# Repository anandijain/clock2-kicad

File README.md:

# clock2-kicad

the ben eater clock module as a pcb

I'm not sure why the placement of the resistors, caps, and 555s (and a few other things) is wrong in the 3D file.

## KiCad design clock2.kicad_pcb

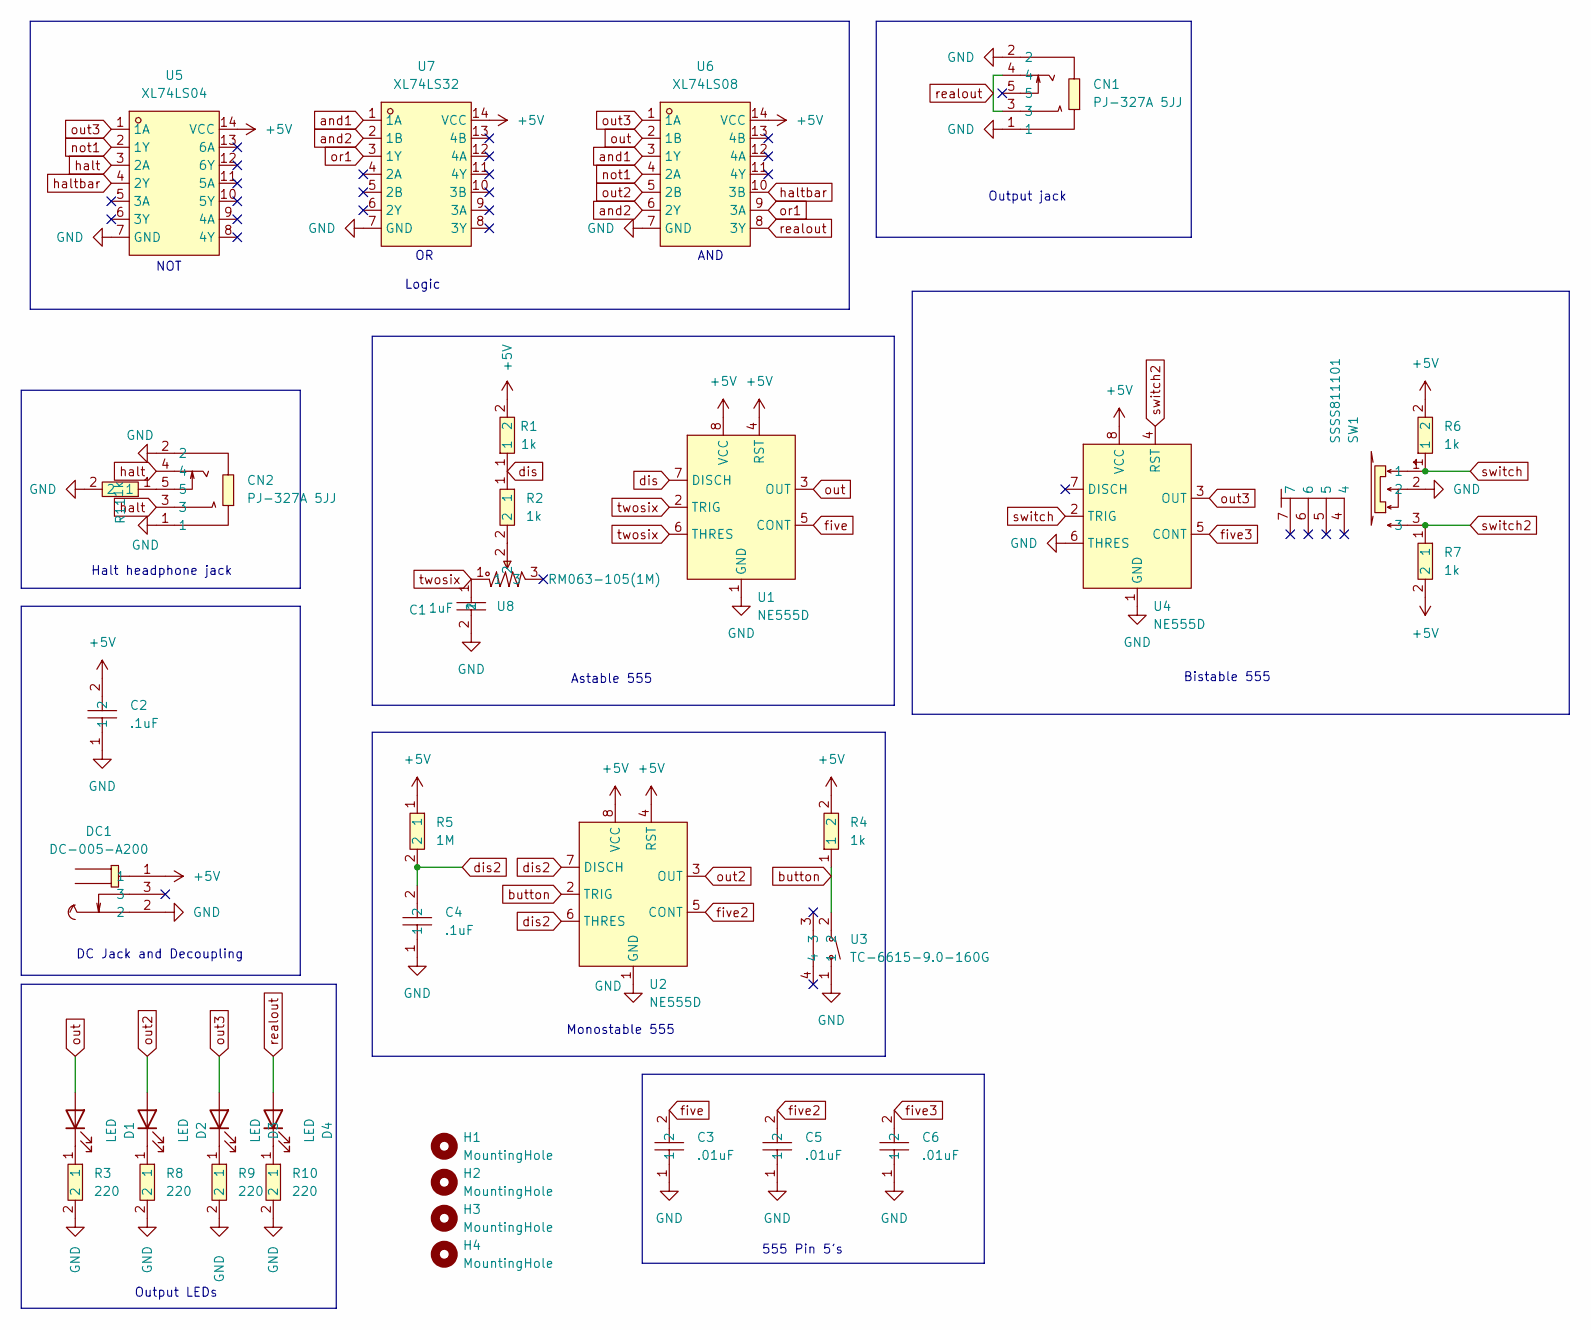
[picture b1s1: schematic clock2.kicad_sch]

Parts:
C1: 1uF; C0805; LCSC Part C28323
C2, C4: .1uF; C0805; LCSC Part C49678
C3, C5, C6: .01uF; C0805; LCSC Part C83170
CN1, CN2: PJ-327A 5JJ; AUDIO-SMD_PJ-327A5JJ; LCSC Part C668605
D1, D2, D3, D4: LED; LED_D5.0mm
DC1: DC-005-A200; DC-IN-TH_DC-005-A200; LCSC Part C720557
H1, H2, H3, H4: MountingHole; MountingHole_3.2mm_M3
R1, R2, R4, R6, R7, R11: 1k; R0805; LCSC Part C95781
R3, R8, R9, R10: 220; R0805; LCSC Part C17557
R5: 1M; R0805; LCSC Part C107700
SW1: SSSS811101; SW-SMD_SSSS811101; LCSC Part C109335
U1, U2, U4: NE555D; SOIC-8_L4.9-W3.9-P1.27-LS6.0-BL; LCSC Part C7593
U3: TC-6615-9.0-160G; KEY-TH_PTS645VXX83XLFS; LCSC Part C6575016
U5: XL74LS04; SOP-14_L8.6-W3.9-P1.27-LS6.0-BL; LCSC Part C513511
U6: XL74LS08; SOP-14_L8.6-W3.9-P1.27-LS6.0-BL; LCSC Part C521140
U7: XL74LS32; SOP-14_L8.6-W3.9-P1.27-LS6.0-BL; LCSC Part C521171
U8: RM063-105(1M); RES-ADJ-TH_RM063-103; LCSC Part C5205038

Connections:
+5V: C2.2, DC1.1, R1.2, R4.2, R5.1, R6.2, R7.2, U1.4 (RST), U1.8 (VCC), U2.4 (RST), U2.8 (VCC), U4.8 (VCC), U5.14 (VCC), U6.14 (VCC), U7.14 (VCC)
GND: C1.2, C2.1, C3.1, C4.1, C5.1, C6.1, CN1.1, CN1.2, CN2.1, CN2.2, DC1.2, R3.2, R8.2, R9.2, R10.2, R11.2, SW1.2, U1.1 (GND), U2.1 (GND), U3.1, U4.1 (GND), U4.6 (THRES), U5.7 (GND), U6.7 (GND), U7.7 (GND)
unnamed: CN2.5, R11.1
unnamed: D1.1 (K), R3.1
unnamed: D2.1 (K), R8.1
unnamed: D3.1 (K), R9.1
unnamed: D4.1 (K), R10.1
unnamed: R2.2, U8.2
and1: U6.3 (1Y), U7.1 (1A)
and2: U6.6 (2Y), U7.2 (1B)
button: R4.1, U2.2 (TRIG), U3.2
dis: R1.1, R2.1, U1.7 (DISCH)
dis2: C4.2, R5.2, U2.6 (THRES), U2.7 (DISCH)
five: C3.2, U1.5 (CONT)
five2: C5.2, U2.5 (CONT)
five3: C6.2, U4.5 (CONT)
halt: CN2.3, CN2.4, U5.3 (2A)
haltbar: U5.4 (2Y), U6.10 (3B)
not1: U5.2 (1Y), U6.4 (2A)
or1: U6.9 (3A), U7.3 (1Y)
out: D1.2 (A), U1.3 (OUT), U6.2 (1B)
out2: D2.2 (A), U2.3 (OUT), U6.5 (2B)
out3: D3.2 (A), U4.3 (OUT), U5.1 (1A), U6.1 (1A)
realout: CN1.3, CN1.4, D4.2 (A), U6.8 (3Y)
switch: R6.1, SW1.1, U4.2 (TRIG)
switch2: R7.1, SW1.3, U4.4 (RST)
twosix: C1.1, U1.2 (TRIG), U1.6 (THRES), U8.1

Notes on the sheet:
Output LEDs
Bistable 555
Monostable 555
Output jack
Halt headphone jack
DC Jack and Decoupling
AND
NOT
555 Pin 5's
Logic
Astable 555

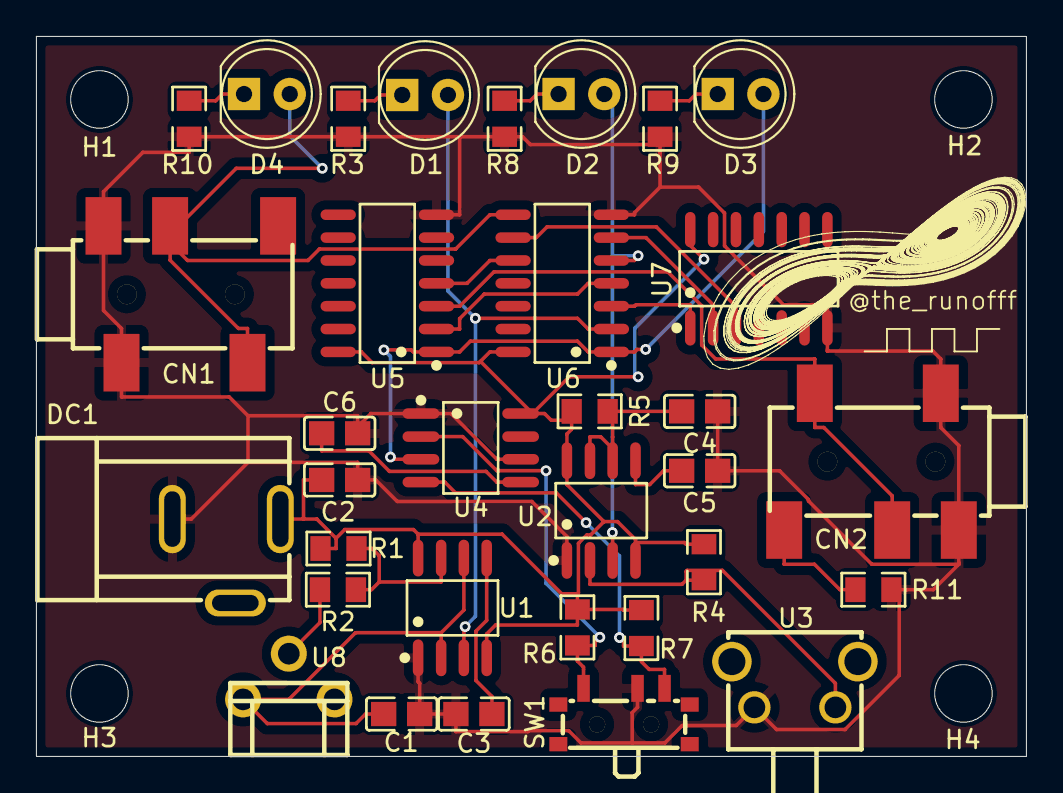
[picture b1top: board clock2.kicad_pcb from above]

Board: 2 copper layers, 55.0 x 40.0 mm, 37 parts (0 on the bottom side), 27 nets.

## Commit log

2025-07-30 init
2025-07-30 use the switching capability of the headphone jack to default the HALT signal to LOW. use resistor to prevent input HALT short to ground before contact breaks
2025-07-30 v1 finalized
2025-07-31 images in readme
2025-07-31 fix links?
